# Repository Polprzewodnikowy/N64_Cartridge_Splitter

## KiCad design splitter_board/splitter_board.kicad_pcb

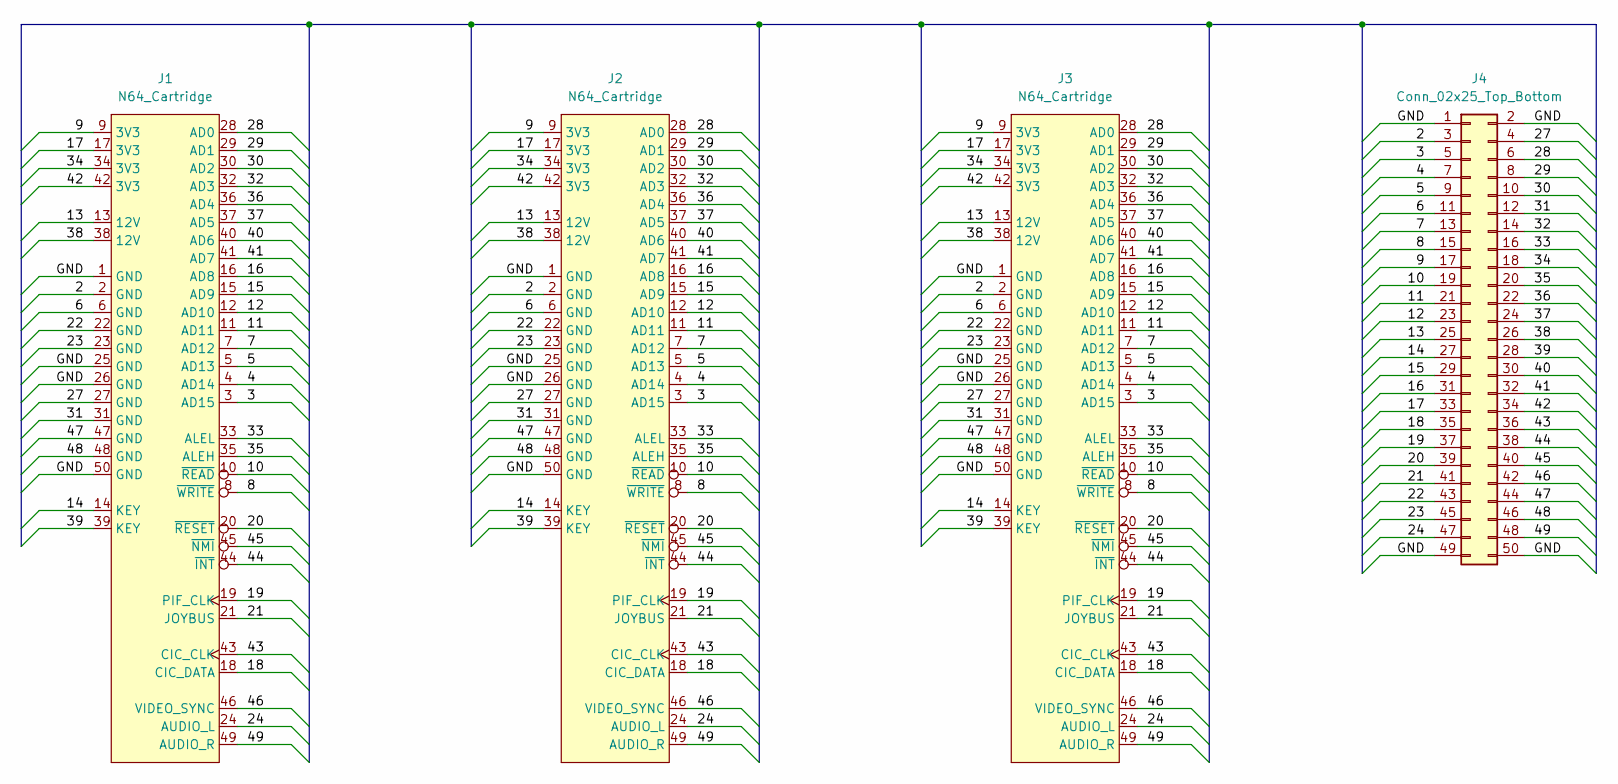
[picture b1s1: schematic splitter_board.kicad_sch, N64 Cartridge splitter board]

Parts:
J1, J2, J3: N64_Cartridge; N64_Slot
J4: Conn_02x25_Top_Bottom; PinHeader_2x25_P2.54mm_Vertical

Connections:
/2: J1.2 (GND), J2.2 (GND), J3.2 (GND), J4.3
/3: J1.3 (AD15), J2.3 (AD15), J3.3 (AD15), J4.5
/4: J1.4 (AD14), J2.4 (AD14), J3.4 (AD14), J4.7
/5: J1.5 (AD13), J2.5 (AD13), J3.5 (AD13), J4.9
/6: J1.6 (GND), J2.6 (GND), J3.6 (GND), J4.11
/7: J1.7 (AD12), J2.7 (AD12), J3.7 (AD12), J4.13
/8: J1.8 (~WRITE), J2.8 (~WRITE), J3.8 (~WRITE), J4.15
/9: J1.9 (3V3), J2.9 (3V3), J3.9 (3V3), J4.17
/10: J1.10 (~READ), J2.10 (~READ), J3.10 (~READ), J4.19
/11: J1.11 (AD11), J2.11 (AD11), J3.11 (AD11), J4.21
/12: J1.12 (AD10), J2.12 (AD10), J3.12 (AD10), J4.23
/13: J1.13 (12V), J2.13 (12V), J3.13 (12V), J4.25
/14: J1.14 (KEY), J2.14 (KEY), J3.14 (KEY), J4.27
/15: J1.15 (AD9), J2.15 (AD9), J3.15 (AD9), J4.29
/16: J1.16 (AD8), J2.16 (AD8), J3.16 (AD8), J4.31
/17: J1.17 (3V3), J2.17 (3V3), J3.17 (3V3), J4.33
/18: J1.18 (CIC_DATA), J2.18 (CIC_DATA), J3.18 (CIC_DATA), J4.35
/19: J1.19 (PIF_CLK), J2.19 (PIF_CLK), J3.19 (PIF_CLK), J4.37
/20: J1.20 (~RESET), J2.20 (~RESET), J3.20 (~RESET), J4.39
/21: J1.21 (JOYBUS), J2.21 (JOYBUS), J3.21 (JOYBUS), J4.41
/22: J1.22 (GND), J2.22 (GND), J3.22 (GND), J4.43
/23: J1.23 (GND), J2.23 (GND), J3.23 (GND), J4.45
/24: J1.24 (AUDIO_L), J2.24 (AUDIO_L), J3.24 (AUDIO_L), J4.47
/27: J1.27 (GND), J2.27 (GND), J3.27 (GND), J4.4
/28: J1.28 (AD0), J2.28 (AD0), J3.28 (AD0), J4.6
/29: J1.29 (AD1), J2.29 (AD1), J3.29 (AD1), J4.8
/30: J1.30 (AD2), J2.30 (AD2), J3.30 (AD2), J4.10
/31: J1.31 (GND), J2.31 (GND), J3.31 (GND), J4.12
/32: J1.32 (AD3), J2.32 (AD3), J3.32 (AD3), J4.14
/33: J1.33 (ALEL), J2.33 (ALEL), J3.33 (ALEL), J4.16
/34: J1.34 (3V3), J2.34 (3V3), J3.34 (3V3), J4.18
/35: J1.35 (ALEH), J2.35 (ALEH), J3.35 (ALEH), J4.20
/36: J1.36 (AD4), J2.36 (AD4), J3.36 (AD4), J4.22
/37: J1.37 (AD5), J2.37 (AD5), J3.37 (AD5), J4.24
/38: J1.38 (12V), J2.38 (12V), J3.38 (12V), J4.26
/39: J1.39 (KEY), J2.39 (KEY), J3.39 (KEY), J4.28
/40: J1.40 (AD6), J2.40 (AD6), J3.40 (AD6), J4.30
/41: J1.41 (AD7), J2.41 (AD7), J3.41 (AD7), J4.32
/42: J1.42 (3V3), J2.42 (3V3), J3.42 (3V3), J4.34
/43: J1.43 (CIC_CLK), J2.43 (CIC_CLK), J3.43 (CIC_CLK), J4.36
/44: J1.44 (~INT), J2.44 (~INT), J3.44 (~INT), J4.38
/45: J1.45 (~NMI), J2.45 (~NMI), J3.45 (~NMI), J4.40
/46: J1.46 (VIDEO_SYNC), J2.46 (VIDEO_SYNC), J3.46 (VIDEO_SYNC), J4.42
/47: J1.47 (GND), J2.47 (GND), J3.47 (GND), J4.44
/48: J1.48 (GND), J2.48 (GND), J3.48 (GND), J4.46
/49: J1.49 (AUDIO_R), J2.49 (AUDIO_R), J3.49 (AUDIO_R), J4.48
/GND: J1.1 (GND), J1.25 (GND), J1.26 (GND), J1.50 (GND), J2.1 (GND), J2.25 (GND), J2.26 (GND), J2.50 (GND), J3.1 (GND), J3.25 (GND), J3.26 (GND), J3.50 (GND), J4.1, J4.2, J4.49, J4.50

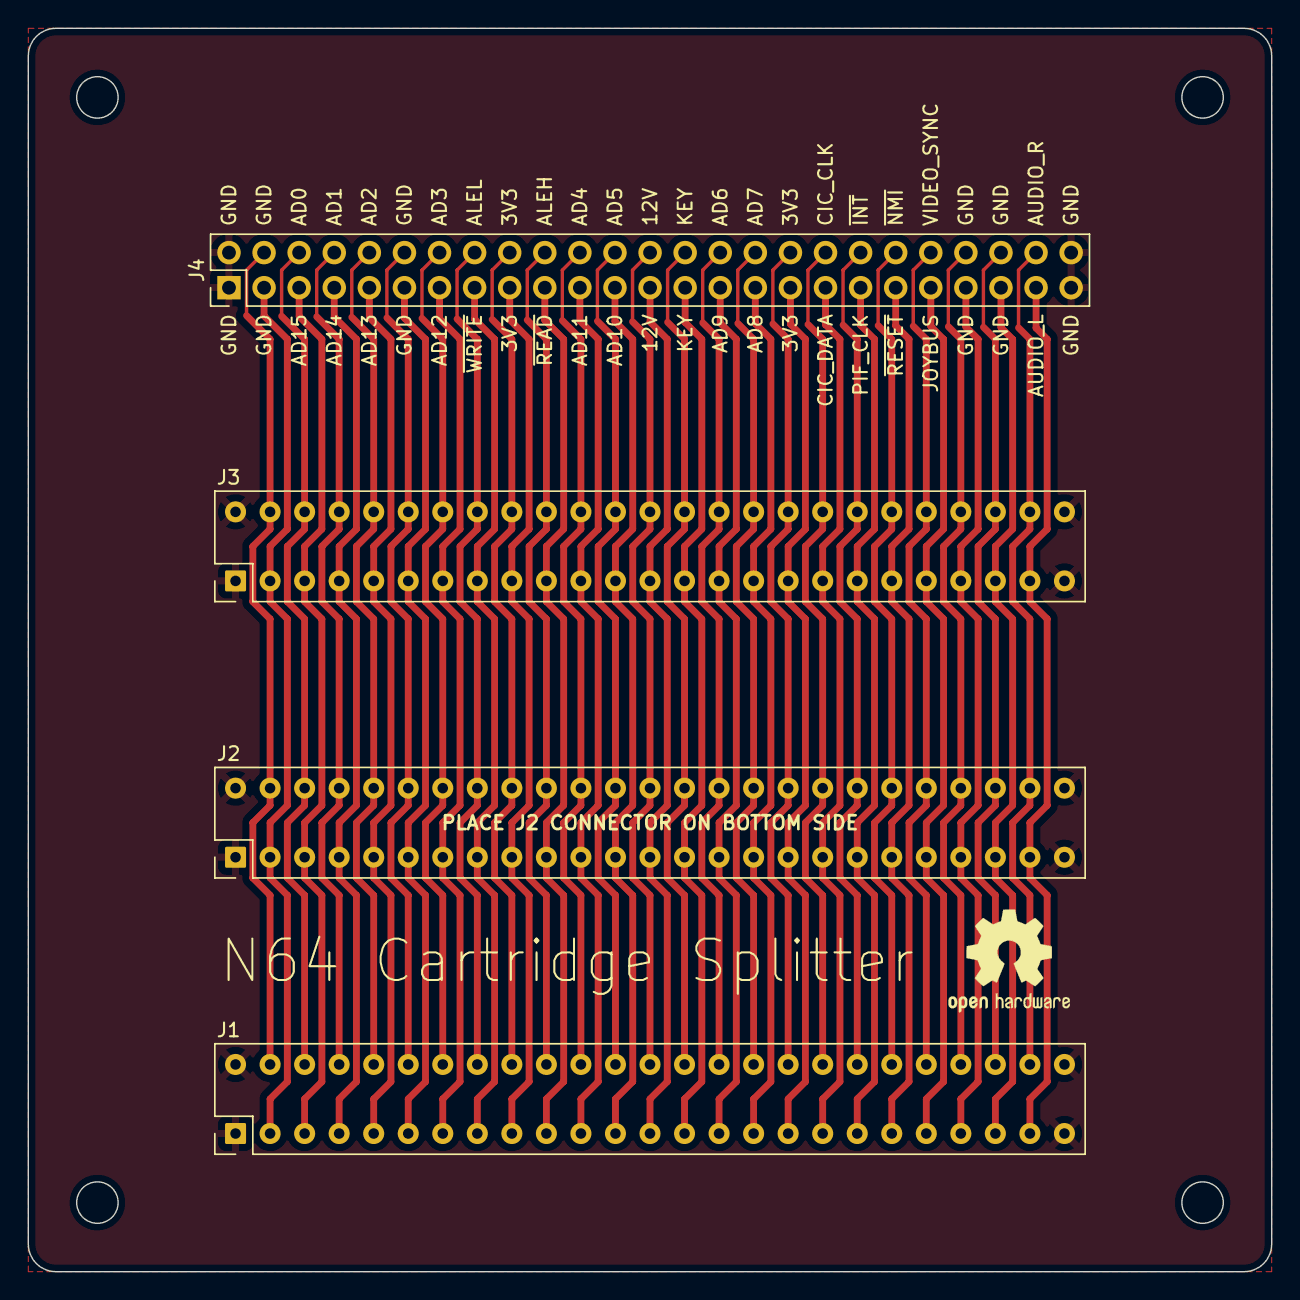
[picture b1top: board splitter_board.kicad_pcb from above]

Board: 2 copper layers, 90.0 x 90.0 mm, 4 parts (0 on the bottom side), 47 nets.

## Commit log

2022-01-02 v1.0
